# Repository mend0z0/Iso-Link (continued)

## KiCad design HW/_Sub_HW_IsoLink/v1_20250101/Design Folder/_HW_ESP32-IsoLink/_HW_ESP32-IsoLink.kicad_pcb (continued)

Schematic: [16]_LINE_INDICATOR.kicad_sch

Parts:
D1901: Orange_2V_605nm; LED_0603_1608Metric; MPN 1 B1911UD--20D001014U1930
D1902: Blue_3.3V_470nm; LED_0603_1608Metric; MPN 1 B1931NB--20C007614U1930
R1901: 330R_1/10W_1%; R_0603_1608Metric; MPN 1 CRG0603F330R
U1901, U1902: 74AHC1G79GW,125; SOT-353_SC-70-5; MPN 1 74AHC1G79GW,125

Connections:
+5V: R1901.1, U1901.5 (VCC), U1902.5 (VCC); also elsewhere on the board
/BLOCK DIAGRAM/1-1 BI-DIR ISOLATOR/ISO6521_INA: U1902.1 (D); also elsewhere on the board
/BLOCK DIAGRAM/1-1 BI-DIR ISOLATOR/ISO6521_OUTB: U1901.1 (D); also elsewhere on the board
/BLOCK DIAGRAM/CAN DRIVER/LINE_INDICATOR1/CLOCK: U1901.2 (CP), U1902.2 (CP); also elsewhere on the board
GND2: U1901.3 (GND), U1902.3 (GND); also elsewhere on the board
unnamed: D1901.2, D1902.2, R1901.2
unnamed: D1901.1, U1901.4 (Q)
unnamed: D1902.1, U1902.4 (Q)

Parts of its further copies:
D2001, D2101, D2201: Orange_2V_605nm; LED_0603_1608Metric; MPN 1 B1911UD--20D001014U1930
D2002, D2102, D2202: Blue_3.3V_470nm; LED_0603_1608Metric; MPN 1 B1931NB--20C007614U1930
R2001, R2101, R2201: 330R_1/10W_1%; R_0603_1608Metric; MPN 1 CRG0603F330R
U2001, U2002, U2101, U2102, U2201, U2202: 74AHC1G79GW,125; SOT-353_SC-70-5; MPN 1 74AHC1G79GW,125

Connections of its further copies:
+5V: R2001.1, R2101.1, R2201.1, U2001.5 (VCC), U2002.5 (VCC), U2101.5 (VCC), U2102.5 (VCC), U2201.5 (VCC), U2202.5 (VCC); also elsewhere on the board
/BLOCK DIAGRAM/1-1 BI-DIR ISOLATOR1/ISO6521_INA: U2002.1 (D); also elsewhere on the board
/BLOCK DIAGRAM/1-1 BI-DIR ISOLATOR1/ISO6521_OUTB: U2001.1 (D); also elsewhere on the board
/BLOCK DIAGRAM/1-1 BI-DIR ISOLATOR2/ISO6521_INA: U2102.1 (D); also elsewhere on the board
/BLOCK DIAGRAM/1-1 BI-DIR ISOLATOR2/ISO6521_OUTB: U2101.1 (D); also elsewhere on the board
/BLOCK DIAGRAM/1-1 BI-DIR ISOLATOR3/ISO6521_INA: U2202.1 (D); also elsewhere on the board
/BLOCK DIAGRAM/1-1 BI-DIR ISOLATOR3/ISO6521_OUTB: U2201.1 (D); also elsewhere on the board
/BLOCK DIAGRAM/CAN DRIVER/LINE_INDICATOR1/CLOCK: U2001.2 (CP), U2002.2 (CP), U2101.2 (CP), U2102.2 (CP), U2201.2 (CP), U2202.2 (CP); also elsewhere on the board
GND2: U2001.3 (GND), U2002.3 (GND), U2101.3 (GND), U2102.3 (GND), U2201.3 (GND), U2202.3 (GND); also elsewhere on the board
unnamed: D2001.2, D2002.2, R2001.2
unnamed: D2101.2, D2102.2, R2101.2
unnamed: D2201.2, D2202.2, R2201.2
unnamed: D2001.1, U2001.4 (Q)
unnamed: D2002.1, U2002.4 (Q)
unnamed: D2101.1, U2101.4 (Q)
unnamed: D2102.1, U2102.4 (Q)
unnamed: D2201.1, U2201.4 (Q)
unnamed: D2202.1, U2202.4 (Q)

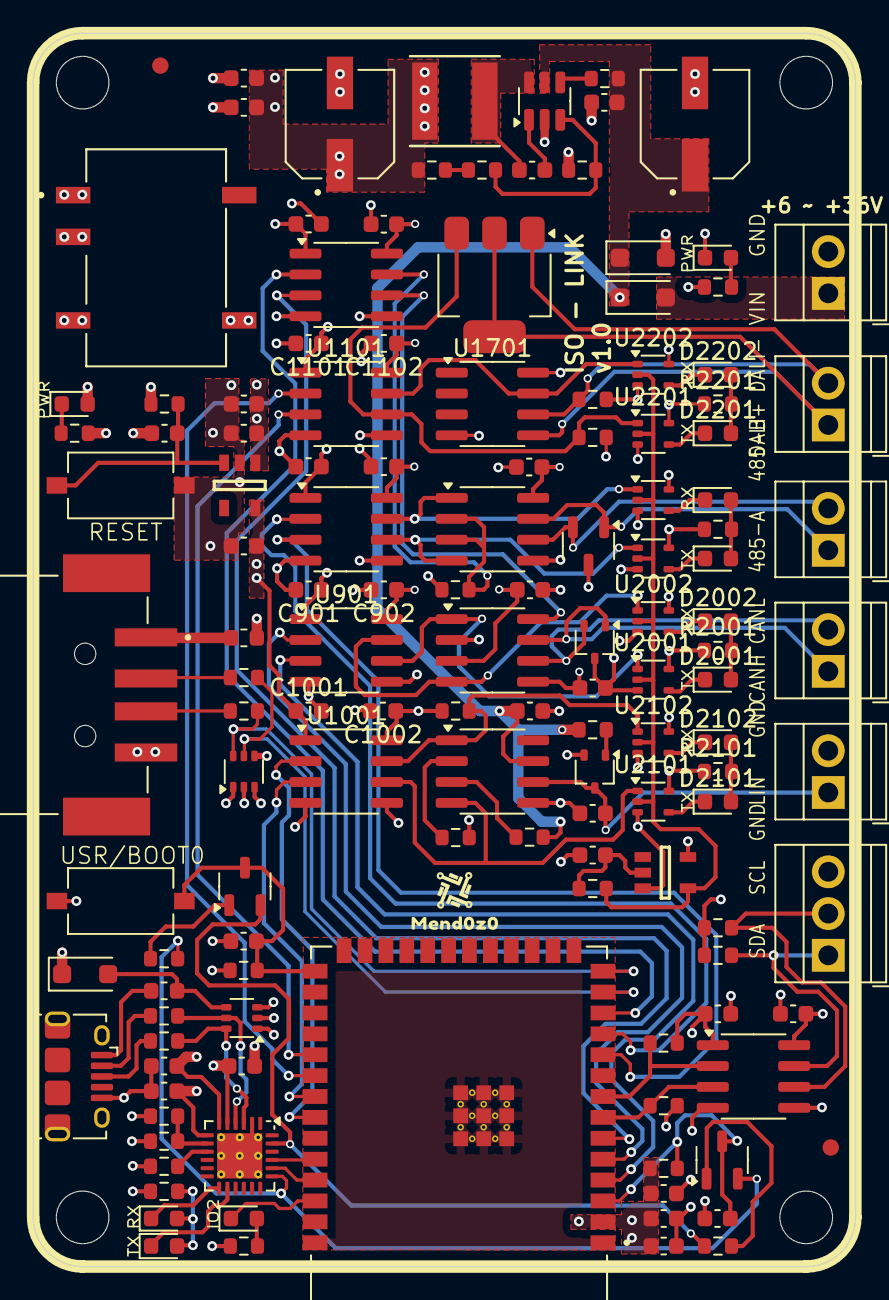
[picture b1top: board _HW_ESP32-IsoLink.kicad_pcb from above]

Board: 4 copper layers, 50.0 x 75.0 mm, 144 parts (0 on the bottom side), 89 nets.

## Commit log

2025-01-23 Create the project repo
